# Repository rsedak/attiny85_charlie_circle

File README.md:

[Croatian version](README_HR-HR.md).

Introduction
============

Purpose of Charlie circle module is student education. It shows advantages of charlieplexing.

Contributor
------------
- Robert Sedak — features, programming, schematic design, CAD design.

Application
-----------
Robert Sedak made a video with example programmed in Arduino IDE with ATtiny85 support:

You can download example for Arduino IDE from [here](examples/).

Bill Of Materials
-----------------
- 1 ea., PCB
- 4 ea., 470R ohm 1/4W 1% Resistor (R1, R2, R3, R4)
- 12 ea., LED 3mm (D1, D2, D3, D4, D5, D6, D7, D8, D9, D10, D11, D12)
- 4 ea., 6x6x4.3mm SPST Momentary push switch (SW1)
- 1 ea., SDPT 1P2T slide switch (SW2)
- 1 ea., 100nF 50V Monolithic Ceramic Capacitor
- 1 ea., 8-Pin DIL IC Socket
- 1 ea., ATtiny85
- 1 ea., 14x7.5mm passive electronic piezoelectric buzzer SE
- 1 ea., battery holder Keystone 1060
- 1 ea., battery 2025

Design Files
------------
This project is designed using Open Source [KiCad](http://kicad.org/). Design files are located in the [design_files](design_files/) folder.  You can see the [schematic](images/charlie_circle_schematic.png).

Gerber files
------------
You can download gerber files from [here](gerber/attiny85_charlie_circle.zip).

Firmware
--------
This project can be programmed using the Open Source [Arduino](https://www.arduino.cc/).
[ATTinyCore by Spence Konde](https://github.com/SpenceKonde/ATTinyCore) was used to program ATtiny85 in Arduino IDE.
Arduino example is located in [examples](examples/) folder.

License
-------
[Attribution-ShareAlike 4.0 International (CC BY-SA 4.0)](https://creativecommons.org/licenses/by-sa/4.0/)

You are free to:
- Share — copy and redistribute the material in any medium or format
- Adapt — remix, transform, and build upon the material

This license is acceptable for Free Cultural Works.
- The licensor cannot revoke these freedoms as long as you follow the license terms.

Under the following terms:
- Attribution — You must give appropriate credit, provide a link to the license, and indicate if changes were made. You may do so in any reasonable manner, but not in any way that suggests the licensor endorses you or your use.
- ShareAlike — If you remix, transform, or build upon the material, you must distribute your contributions under the same license as the original.

No additional restrictions — You may not apply legal terms or technological measures that legally restrict others from doing anything the license permits.

Reference Designs ARE PROVIDED "AS IS" AND "WITH ALL FAULTS". Authors DISCLAIMS ALL OTHER WARRANTIES, EXPRESS OR IMPLIED, REGARDING PRODUCTS, INCLUDING BUT NOT LIMITED TO, ANY IMPLIED WARRANTIES OF MERCHANTABILITY OR FITNESS FOR A PARTICULAR PURPOSE.
Authors may make changes to specifications and product descriptions at any time, without notice. The Customer must notrely on the absence or characteristics of any features or instructions marked "reserved" or "undefined."
Authors reservesthese for future definition and shall have no responsibility whatsoever for conflicts or incompatibilities arising from future changes to them. The product information on the Web Site or Materials is subject to change without notice. Do not finalize a design with this info.

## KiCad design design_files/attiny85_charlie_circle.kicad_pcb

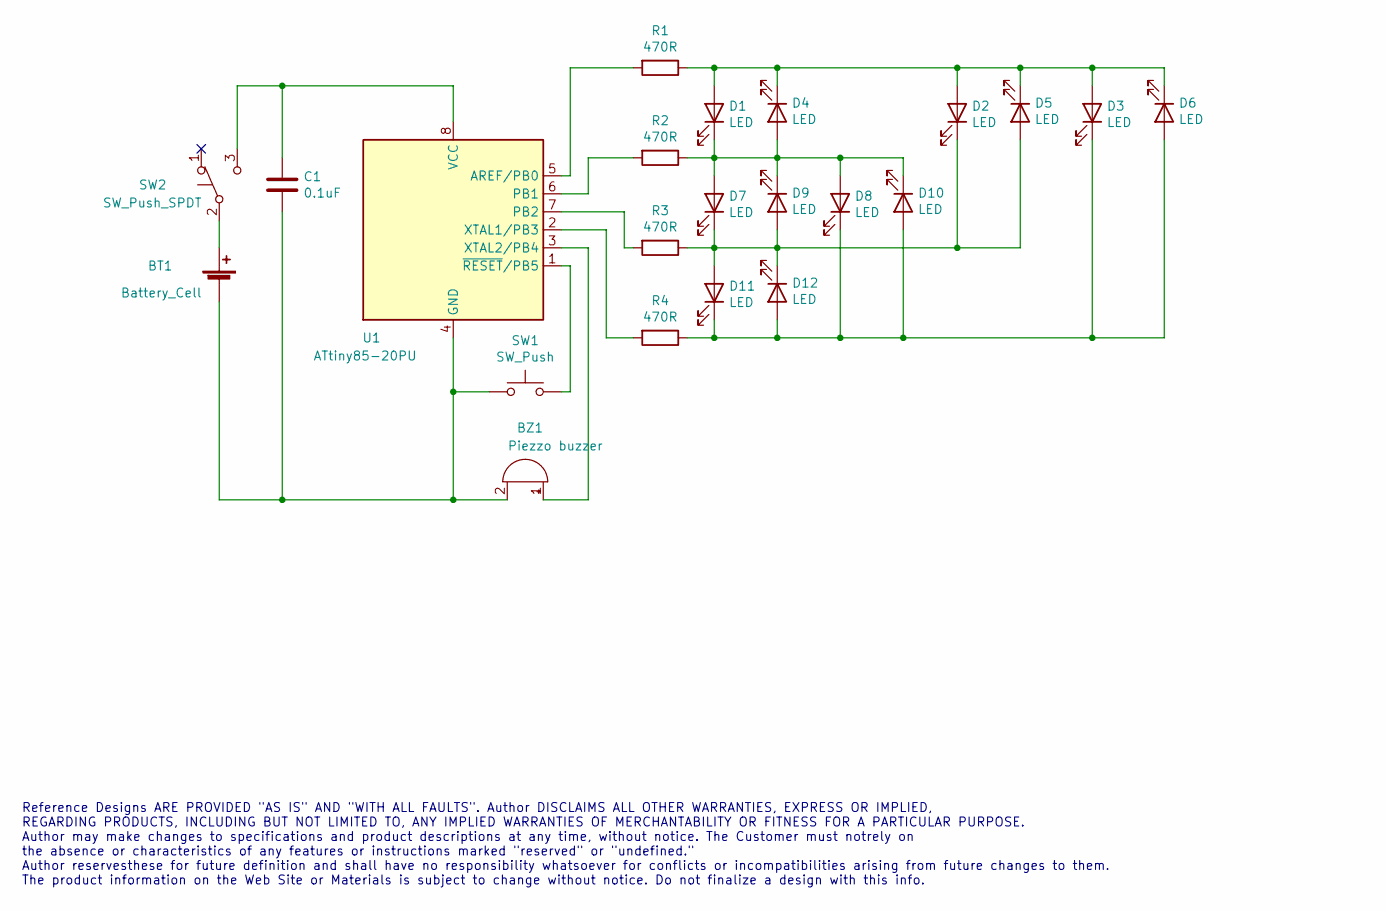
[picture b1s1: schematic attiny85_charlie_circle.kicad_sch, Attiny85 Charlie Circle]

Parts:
BT1: Battery_Cell; BatteryHolder_Keystone_1060_1x2032
BZ1: Piezzo buzzer; Buzzer_12x9.5RM7.6
C1: 0.1uF; C_Rect_L4.6mm_W2.0mm_P2.50mm_MKS02_FKP02
D1, D2, D3, D4, D5, D6, D7, D8, D9, D10, D11, D12: LED; LED_D3.0mm
R1, R2, R3, R4: 470R; R_Axial_DIN0207_L6.3mm_D2.5mm_P7.62mm_Horizontal
SW1: SW_Push; SW_PUSH_6mm_H8mm
SW2: SW_Push_SPDT; SW_Slide_SPDT_1P2T
U1: ATtiny85-20PU; DIP-8_W7.62mm

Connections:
unnamed: BT1.1 (+), SW2.2 (B)
unnamed: BT1.2 (-), BZ1.2 (+), C1.2, SW1.1, U1.4 (GND)
unnamed: BZ1.1 (-), U1.3 (XTAL2/PB4)
unnamed: C1.1, SW2.3 (C), U1.8 (VCC)
unnamed: D1.1 (K), D4.2 (A), D7.2 (A), D8.2 (A), D9.1 (K), D10.1 (K), R2.1
unnamed: D1.2 (A), D2.2 (A), D3.2 (A), D4.1 (K), D5.1 (K), D6.1 (K), R1.1
unnamed: D3.1 (K), D6.2 (A), D8.1 (K), D10.2 (A), D11.1 (K), D12.2 (A), R4.1
unnamed: D2.1 (K), D5.2 (A), D7.1 (K), D9.2 (A), D11.2 (A), D12.1 (K), R3.1
unnamed: R1.2, U1.5 (AREF/PB0)
unnamed: R2.2, U1.6 (PB1)
unnamed: R3.2, U1.7 (PB2)
unnamed: R4.2, U1.2 (XTAL1/PB3)
unnamed: SW1.2, U1.1 (~RESET/PB5)

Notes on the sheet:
Reference Designs ARE PROVIDED "AS IS" AND "WITH ALL FAULTS". Author DISCLAIMS ALL OTHER WARRANTIES, EXPRESS OR IMPLIED, REGARDING PRODUCTS, INCLUDING BUT NOT LIMITED TO, ANY IMPLIED WARRANTIES OF MERCHANTABILITY OR FITNESS FOR A PARTICULAR PURPOSE. Author may make changes to specifications and pro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

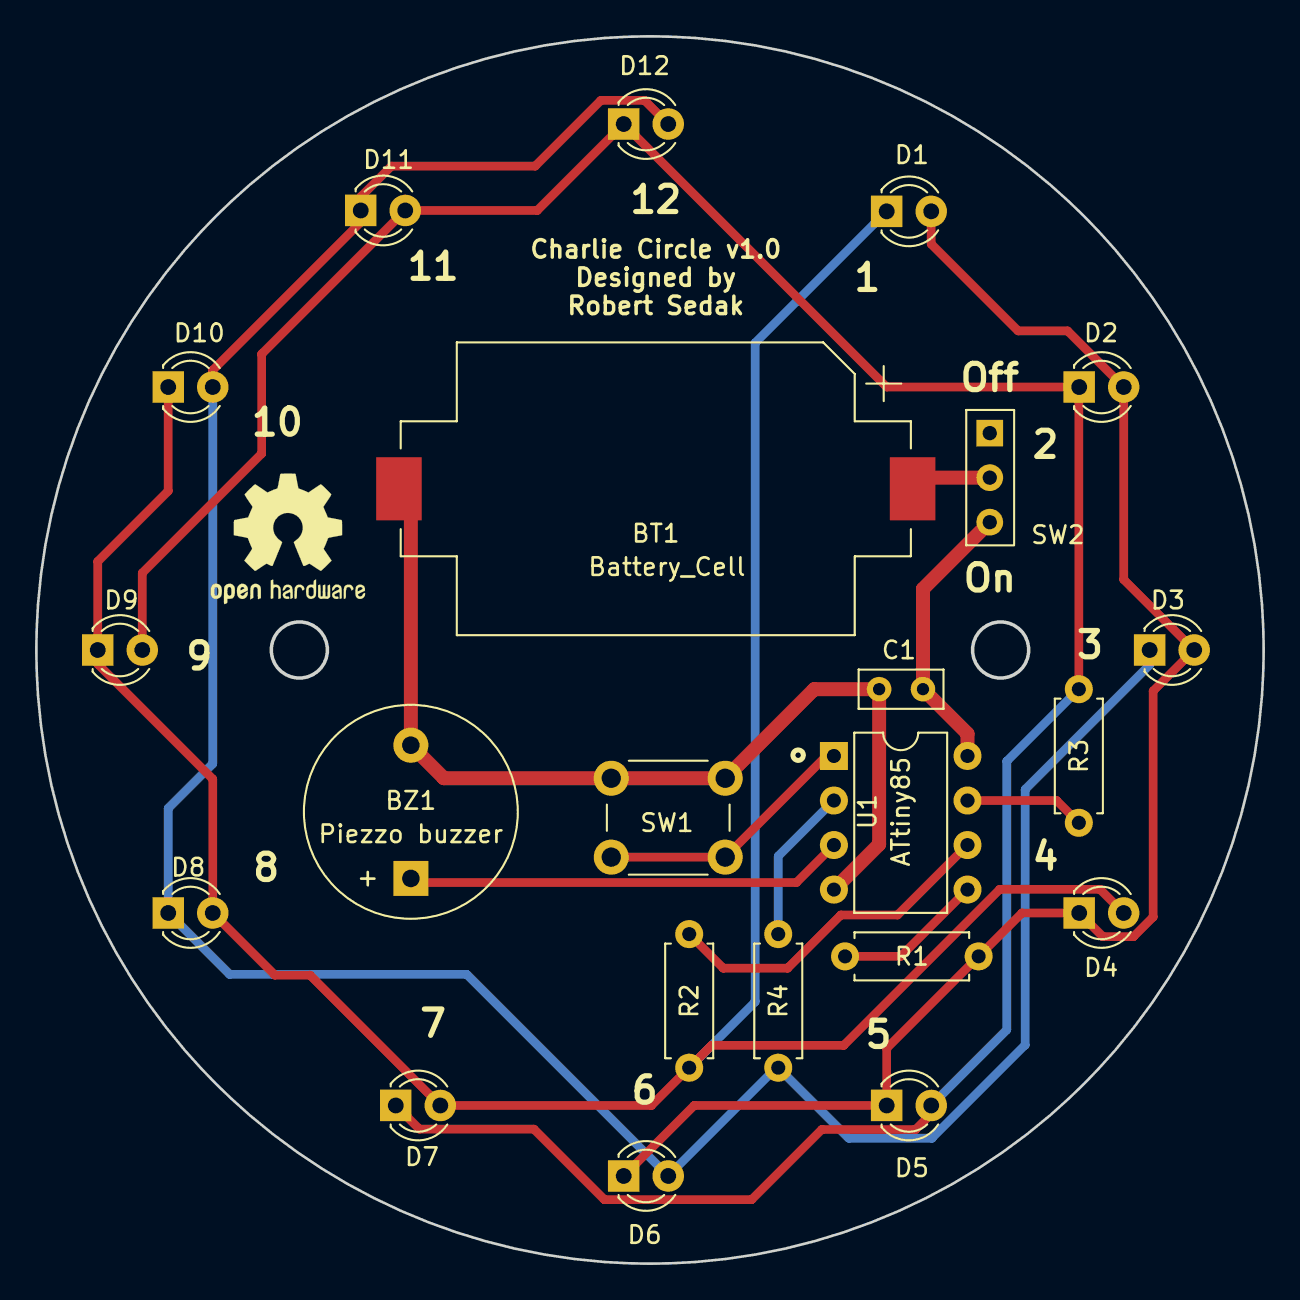
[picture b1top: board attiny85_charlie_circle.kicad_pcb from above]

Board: 2 copper layers, 70.0 x 70.0 mm, 23 parts (0 on the bottom side), 13 nets.

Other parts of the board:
OSHW: OSHW-Logo2_9.8x8mm_SilkScreen

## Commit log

2022-12-11 directory firmware renamed to examples
2022-12-11 Update README_HR-HR.md: Small change

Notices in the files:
design_files/attiny85_charlie_circle.kicad_pcb:
License: CC-BY-SA 4.0
